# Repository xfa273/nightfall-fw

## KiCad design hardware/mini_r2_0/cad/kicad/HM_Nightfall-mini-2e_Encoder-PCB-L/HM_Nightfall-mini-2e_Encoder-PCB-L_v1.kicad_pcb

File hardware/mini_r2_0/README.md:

# hardware/mini_r2_0

STM32F413 系 mini 新機体 (`mini_r2_0`) のハードウェア情報です。

## 構成

- `cad/`: Eagle 回路図・基板・PDF・DRC ルール
- `cad/eagle/`: Eagle 移行前原本
- `cad/kicad/`: KiCad 移行後の編集原本
- `cad/export/`: PDF、Gerber、実装位置、発注用出力
- `bom/`: 部品表・調達情報
- `notes/`: ピン一覧、ERC/DRC スクリーンショット

## 備考

- 主要ソースは `_sandbox/f413_preorder/` から本ディレクトリへ移行済みです。
- 以後の更新は `hardware/mini_r2_0/` 側を正として管理します。
- 対応する Eagle プロジェクトは `HM_Nightfall-mini-2e` です。
- 対応するソフトウェア側プロファイルは `f413_preorder` です。
- KiCad 10.0.3 で `cad/kicad/HM_Nightfall-mini-2e/` へ初回インポート済みです。
- 初回インポート結果は `notes/kicad/` の ERC/DRC レポートを確認しながらレビューします。
- KiCad レビュー完了までは Eagle 原本と KiCad 原本を併存させ、確認後に `cad/kicad/` を編集正とします。

## KiCad プロジェクト単位

- `cad/kicad/HM_Nightfall-mini-2e/`: 本体基板
- `cad/kicad/HM_Nightfall-mini-2e_Encoder-PCB-L/`: 左エンコーダ基板
- `cad/kicad/HM_Nightfall-mini-2e_Encoder-PCB-R/`: 右エンコーダ基板
- `cad/kicad/STLink-Adapter/`: ST-LINK から機体コネクタへの変換基板
- `cad/kicad/UART-Adapter/`: UART から機体コネクタへの変換基板
- `cad/kicad/WeAct-Adapter-5V/`: WeAct MiniDebugger用、手動5 V遮断スイッチ付き変換基板

各サブ基板は本体基板と独立した小基板のため、KiCad でも 1 基板 1 プロジェクトとして管理します。
- Eagle 9.6.2 で生成した参照アーカイブは `cad/export/reference/eagle_archive_20260606/` に保存しています。

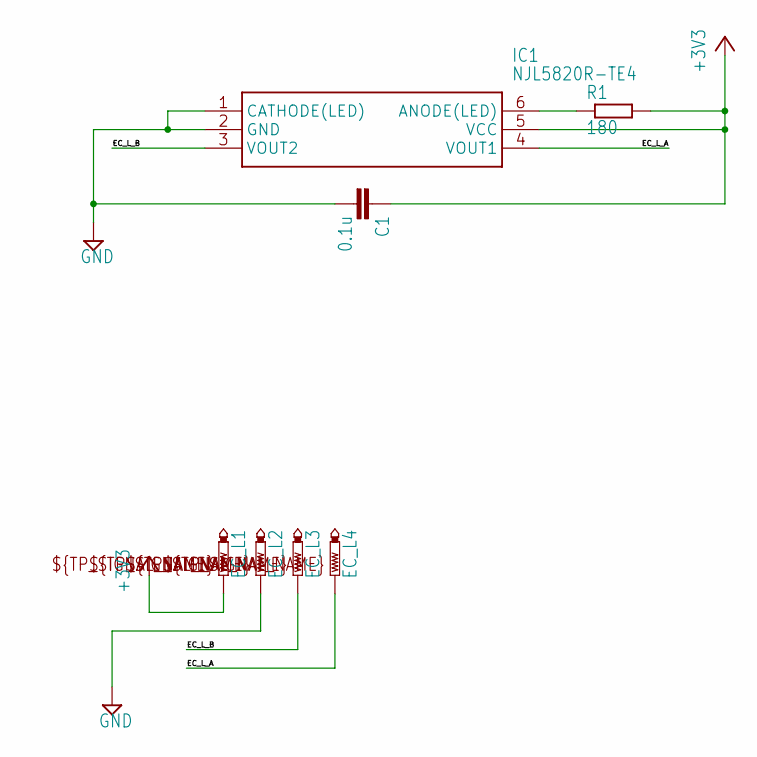
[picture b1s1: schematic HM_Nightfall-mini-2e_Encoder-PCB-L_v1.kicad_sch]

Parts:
C1: 0.1u; C0402
EC_L1, EC_L2, EC_L3, EC_L4: PTR1TP06SQ; TP06SQ
IC1: NJL5820R-TE4; NJL5820RTE4
R1: 180; R0402

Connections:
+3V3: C1.1, EC_L1.TP, IC1.5 (VCC), R1.2
EC_L_A: EC_L4.TP, IC1.4 (VOUT1)
EC_L_B: EC_L3.TP, IC1.3 (VOUT2)
GND: C1.2, EC_L2.TP, IC1.1 (CATHODE(LED)), IC1.2 (GND)
unnamed: IC1.6 (ANODE(LED)), R1.1

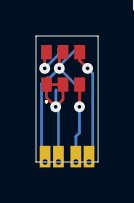
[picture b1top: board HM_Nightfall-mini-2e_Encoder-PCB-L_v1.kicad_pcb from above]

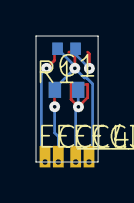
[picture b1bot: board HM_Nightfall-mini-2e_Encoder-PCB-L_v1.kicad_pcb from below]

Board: 2 copper layers, 3.4 x 7.0 mm, 7 parts (6 on the bottom side), 5 nets.

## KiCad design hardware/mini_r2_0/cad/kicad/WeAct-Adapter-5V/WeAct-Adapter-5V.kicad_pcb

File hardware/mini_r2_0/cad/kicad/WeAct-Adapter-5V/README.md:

# WeAct-Adapter-5V

WeAct Studio MiniDebugger から `mini_r2_0` / F413 機体へ SWD、SWO、UART、5 V を接続する変換基板です。
既存の `STLink-Adapter` を基に、デバッガの 5 V 出力を手動で遮断できるスライドスイッチ `SW1` を追加しています。

## 電源スイッチ

- `5V` 側: MiniDebugger の 5 V を機体コネクタ K1 pin 1 へ接続します。
- `OFF` 側: MiniDebugger の 5 V を機体から切り離します。SWD/UART/GND は接続されたままです。
- `SW1` は UART-Adapter と同じ E-Switch `EG1218`（SPDT, On-On）を使用します。中央端子を機体 5 V、`5V` 側端子をデバッガ 5 V、`OFF` 側端子を未接続としています。

> [!CAUTION]
> この基板はダイオードORやロードスイッチによる自動逆流防止回路ではありません。バッテリを接続する前に必ず `OFF` にしてください。`5V` のままバッテリとMiniDebuggerを同時接続しないでください。

`EG1218` の定格は 200 mA / 30 VDC です。このアダプタからの給電はファームウェア書き込み、ログ確認、ブザー等の低消費電力なベンチ作業向けです。モータやファンを動かす用途には使用しません。

## MiniDebugger側の配線

| MiniDebugger信号 | J2 pin | アダプタ | 機体側 |
| --- | --- | --- | --- |
| `5V` | 1 | TP1 pad 1 | K1 pin 1 `+5V`（SW1経由） |
| `TXD` | 4 | TP1 pad 2 | K1 pin 9 `USART1_RX` |
| `RXD` | 3 | TP1 pad 3 | K1 pin 8 `USART1_TX` |
| `GND` | 2 | TP1 pad 4 | K1 pin 2 `GND` |
| `SWDIO` | 9 | TP2 pad 1 | K1 pin 3 `SWDIO` |
| `SWCLK` | 8 | TP2 pad 2 | K1 pin 4 `SWCLK` |
| `SWO` | 6 | TP2 pad 3 | K1 pin 10 `SWO` |

信号名とMiniDebuggerのJ2ピン番号を基準に配線し、コネクタを見たときの物理的な並びだけで判断しないでください。TXD/RXDやSWD信号を5 V/GNDへ誤接続すると、MiniDebuggerのUSB認識が消えるほどの過電流になる場合があります。

MiniDebugger の `3V3`（J2 pin 10）と `NRST`（J2 pin 5）はこのアダプタでは未接続です。余った線は互いに接触しないよう個別に絶縁します。MiniDebugger の2本目の `GND`（J2 pin 7）は未使用でも構いません。

## 初回組立後の確認

最初に機体を接続せず、テスターで次を確認します。

1. `OFF` 側で TP1 pad 1 と K1 pin 1 が導通しないこと。
2. `5V` 側で TP1 pad 1 と K1 pin 1 が導通すること。
3. `5V` 側、`OFF` 側のどちらでも 5 V と GND が短絡していないこと。
4. MiniDebuggerだけを接続し、`5V` 側で K1 pin 1 が約 5 V、`OFF` 側で無給電になること。
5. すべての電源を外して機体側ケーブルを接続し、TP1 pad 4－機体GNDがほぼ0 Ωであること。
6. 同じ状態でTP1 pad 2－機体K1 pin 9、TP2 pad 3－機体K1 pin 10がそれぞれ導通し、5 V/GNDとは短絡していないこと。
7. 最後に機体を接続し、モータ・ファンを動かさずSWD、UART、ブザーを確認すること。

## 検証結果

KiCad 10.0.3 のCLIで確認しています。

- PCB DRC: errors 0、unconnected 0
- DRC warnings: 26（元のSTLink-Adapterと同数。K1の狭ピッチ端子に対する既知のソルダーマスク警告）
- ERC: errors 3、warnings 6（元設計の電源駆動未定義3件とフットプリントライブラリ未登録等。今回追加した配線の未接続・短絡エラーなし）
- 上面・下面3Dレンダリング: `preview/`
- ERC/DRCレポート: `reports/`

### 実機検証（2026-07-27）

初回の外部配線誤りを修正した後、製造した基板とmini_r2_0 / STM32F413機体で次を確認しました。

- `5V` 側で意図どおり5 Vを給電し、`OFF` 側でMiniDebuggerの5 V出力を機体から切り離せること。
- macOSからWeAct MiniDebuggerのST-LINK/V2-1（V2J43M28）を認識できること。
- SWD 4000 kHzでターゲット電圧3.22 V、Device ID `0x463`（STM32F413/F423）を読み取り、software resetが成功すること。
- Virtual COM Portを921600 baud / 8N1で開き、安全なUART診断 `i` に対して `[HW-TEST][IMU] WHO_AM_I=0x6B expected=0x6B => PASS` が返ること。

この確認ではモータ・ファンを動作させず、ファームウェア書き込みおよびNVM書き込みも実施していません。

## 発注データ

`fabrication/WeAct-Adapter-5V-gerbers.zip` を基板メーカーへ投入します。

推奨指定:

- 2 layer
- FR-4, 1.6 mm
- 1 oz copper
- HASL lead-free（または通常HASL）
- Solder mask / silkscreen: 任意色

`fabrication/generate_fab.sh` でGerber、Excellon drill、ZIPを再生成できます。

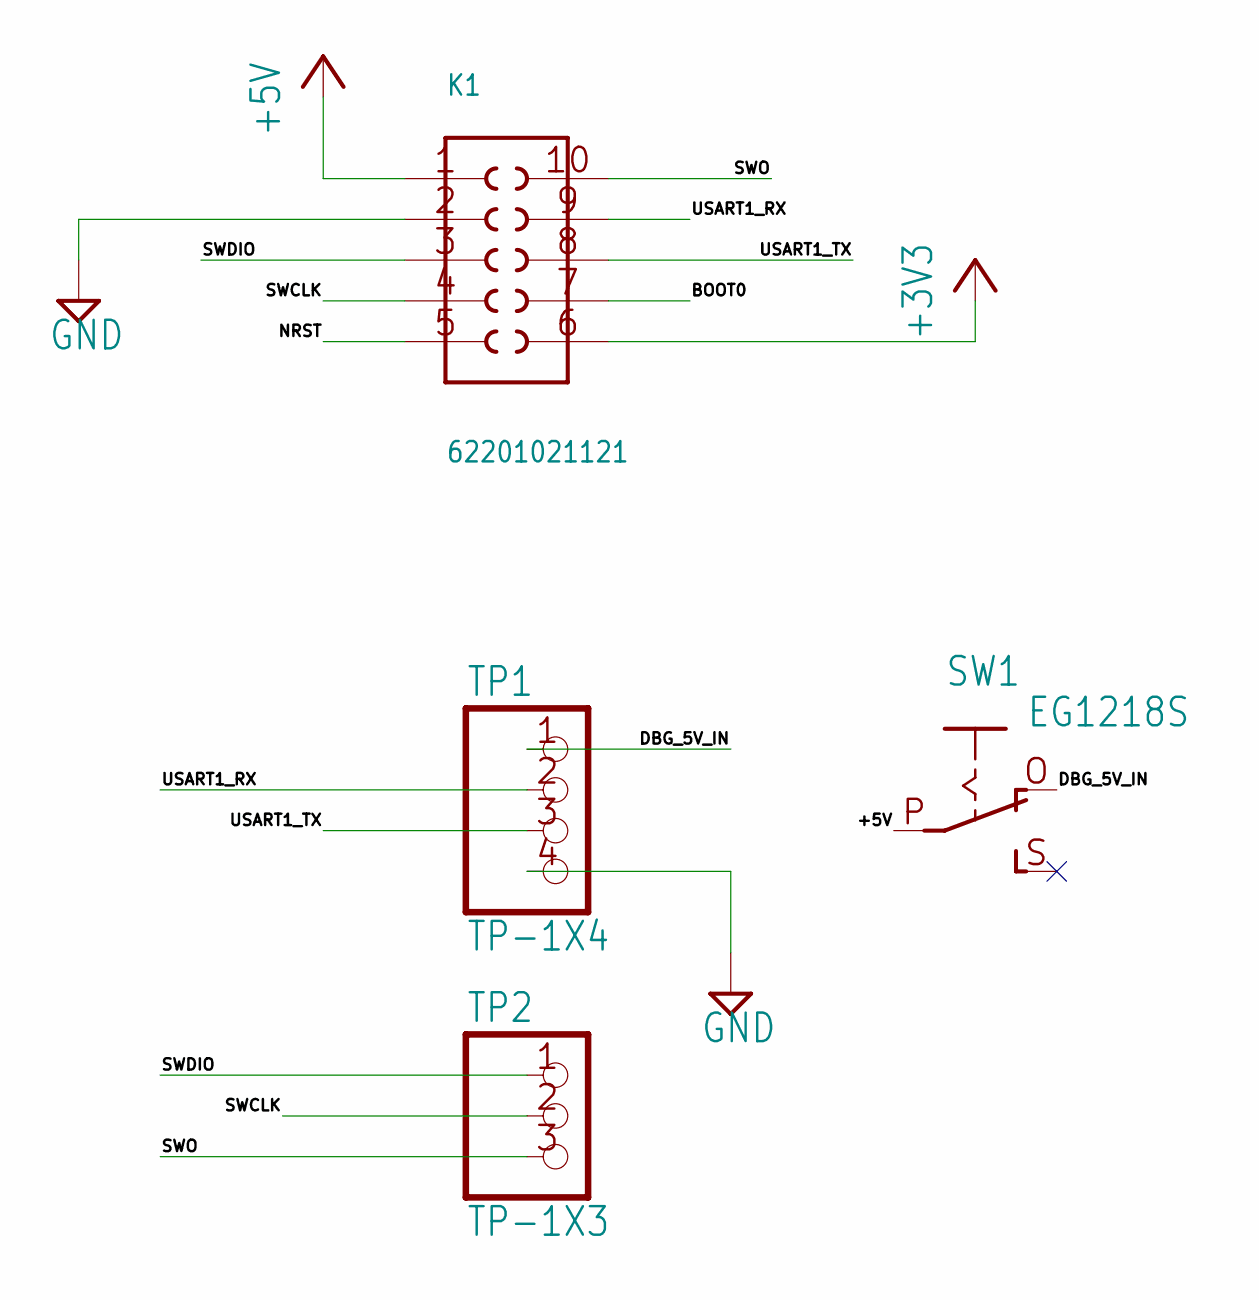
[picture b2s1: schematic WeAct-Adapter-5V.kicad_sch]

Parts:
K1: 62201021121
SW1: EG1218S; EG1218
TP1: TP-1X4; 1X04
TP2: TP-1X3; 1X03

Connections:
+3V3: K1.6
+5V: K1.1, SW1.P
BOOT0: K1.7
DBG_5V_IN: SW1.O, TP1.1
GND: K1.2, TP1.4
NRST: K1.5
SWCLK: K1.4, TP2.2
SWDIO: K1.3, TP2.1
SWO: K1.10, TP2.3
USART1_RX: K1.9, TP1.2
USART1_TX: K1.8, TP1.3

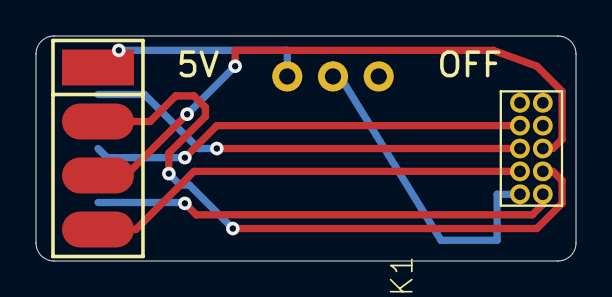
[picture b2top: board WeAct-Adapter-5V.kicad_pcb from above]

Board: 2 copper layers, 30.0 x 12.5 mm, 4 parts (1 on the bottom side), 8 nets.

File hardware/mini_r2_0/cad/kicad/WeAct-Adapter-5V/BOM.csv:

Reference,Quantity,Manufacturer,Manufacturer Part Number,Description,Notes
SW1,1,E-Switch,EG1218,"SPDT On-On through-hole slide switch, 200 mA 30 VDC","Same switch as UART-Adapter"
K1,1,Wurth Elektronik,62201021121,"WR-PHD 1.27 mm dual-row 10-pin header","Confirm mating orientation before soldering"

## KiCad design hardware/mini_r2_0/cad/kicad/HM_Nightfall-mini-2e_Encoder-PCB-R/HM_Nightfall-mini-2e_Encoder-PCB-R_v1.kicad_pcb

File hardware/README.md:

# hardware/

このディレクトリは、機体ごとのハードウェア設計情報の正式置き場です。

## ディレクトリ規約

- `hardware/<board_name>/cad/`: 回路図・基板・設計ルール
- `hardware/<board_name>/cad/eagle/`: Eagle 移行前原本
- `hardware/<board_name>/cad/kicad/`: KiCad 移行後の編集原本
- `hardware/<board_name>/cad/export/`: PDF、Gerber、実装位置、発注用出力
- `hardware/<board_name>/bom/`: 部品表・発注情報
- `hardware/<board_name>/notes/`: 設計メモ・確認結果

`board_name` は `mini_r1_0` のように `<family>_r<major>_<minor>` を使用します。

## Git管理方針

- Eagle の `.sch` / `.brd` / `.dru` / `.cam` と KiCad の `.kicad_pro` / `.kicad_sch` / `.kicad_pcb` は原本として管理します。
- Eagle の `.s#1` / `.b#1` / `.l#1` などの自動バックアップと、KiCad のローカル状態・自動バックアップは管理しません。
- 発注用の Gerber zip や PDF は、再現性が必要な発注版だけを `cad/export/` または GitHub Release で管理します。
- Eagle が使えるうちに確保した旧設計の参照アーカイブは `cad/export/reference/eagle_archive_YYYYMMDD/` に置きます。
- 旧設計や大きな archive は現役基板と分け、必要に応じて別リポジトリ化します。

## 現在の公式配置

- `hardware/mini_r2_0/`: `f413_preorder` / STM32F413 搭載ハーフサイズ / Eagle `HM_Nightfall-mini-2e`
- `hardware/mini_r1_0/`: STM32F405 搭載ハーフサイズ最終版 / Eagle `HM_Nightfall-mini_v1`
- `hardware/classic_r1_0/`: STM32F405 搭載クラシックサイズ最終版 / Eagle `CM_Nightfall-Air_v1`

上記以外の Eagle プロジェクトは旧機体の参考資料として扱い、現役基板とは分けて保管します。

`_sandbox/` 配下は実験・一時作業用とし、正式成果物は本ディレクトリに集約します。

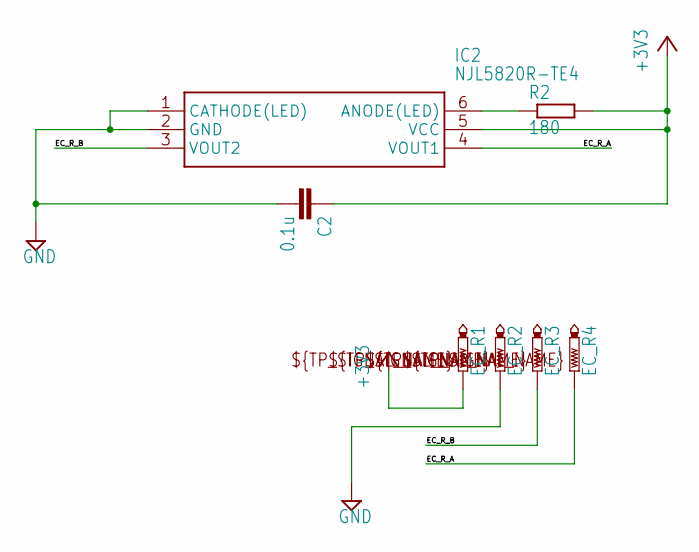
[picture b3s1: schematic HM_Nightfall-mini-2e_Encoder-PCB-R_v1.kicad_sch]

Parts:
C2: 0.1u; C0402
EC_R1, EC_R2, EC_R3, EC_R4: PTR1TP06SQ; TP06SQ
IC2: NJL5820R-TE4; NJL5820RTE4
R2: 180; R0402

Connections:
+3V3: C2.1, EC_R1.TP, IC2.5 (VCC), R2.2
EC_R_A: EC_R4.TP, IC2.4 (VOUT1)
EC_R_B: EC_R3.TP, IC2.3 (VOUT2)
GND: C2.2, EC_R2.TP, IC2.1 (CATHODE(LED)), IC2.2 (GND)
unnamed: IC2.6 (ANODE(LED)), R2.1

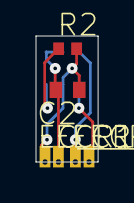
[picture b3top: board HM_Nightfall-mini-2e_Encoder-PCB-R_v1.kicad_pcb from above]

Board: 2 copper layers, 3.4 x 7.0 mm, 7 parts (1 on the bottom side), 5 nets.

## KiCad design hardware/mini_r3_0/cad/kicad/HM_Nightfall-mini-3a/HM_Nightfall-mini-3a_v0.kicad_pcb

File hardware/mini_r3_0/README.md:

# hardware/mini_r3_0

Nightfall mini 3a (`mini_r3_0`) の手動アートワーク開始用データです。

## 開き方

KiCad 10 で次のプロジェクトファイルを開いてください。

`cad/kicad/HM_Nightfall-mini-3a/HM_Nightfall-mini-3a_v0.kicad_pro`

プロジェクトディレクトリには回路図、PCB、設計ルール、ローカルのシンボル／
フットプリントライブラリを同梱しています。別のチェックアウトに依存せず編集できます。

## 引き渡し状態

- 回路図: ERC 0
- PCB: 4層 (`F.Cu / In1.Cu / In2.Cu / B.Cu`)
- 外形、取付穴、機構シルク: 導入済み
- 部品: 102個を配置済み
- 配線、ビア、ゾーン: 0（手動配線開始前）
- U5: 下面露出パッドを使わない手はんだ向けフットプリント
- PCBパッドネット: 最新回路図から再同期済み

未配線なので、PCB DRCの未接続表示が228件あるのは正常です。配線前の物理DRCには
clearance、short、hole、track-crossing、copper-edgeの違反はありません。残る警告は
ライブラリコピー差分とシルク／テキスト由来です。

## 4層の使い方

- `F.Cu / B.Cu`: 部品接続、高電流経路、局所信号
- `In1.Cu`: `GND / GND2` の分割基準面（信号トラックは置かない）
- `In2.Cu`: 低電流信号と `+3V3`
- `GND` と `GND2` は `R0` だけで接続
- 通常信号は 0.20 mm、通常viaは 0.60/0.30 mm
- QFN直近だけ 0.16 mm、局所toe viaは 0.40/0.20 mm
- モータ／ファン約2 A枝は原則0.80 mm以上、集約VBATは1.0 mm以上

回路と電源ドメインの詳細は `notes/POWER_ARCHITECTURE.md` を参照してください。

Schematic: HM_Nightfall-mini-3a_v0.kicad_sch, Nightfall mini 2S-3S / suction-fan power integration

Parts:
C1, C2, C5, C6, C8, C21: 0.1u; C_0402_1005Metric
C3, C15: 2.2u; C0402
C7, C9, C22: 10u/25V X7R; C_0805_2012Metric
C14: 1u; C0402
C23: 22u/10V X7R; C_0805_2012Metric
C24: 0.1u/25V X7R; C_0402_1005Metric
C25: 100nF X7R; C_0402_1005Metric
C_MCU0, C_MCU1, C_MCU2, C_MCU3: 0.1u; C_0402_1005Metric
C_MCU-C0: 2.2u; C_0402_1005Metric
C_MCU-M0: 4.7u; C0402
D3, D4: BAS16WT1GW; SOT323
D5: BZT52-C15S_R1_00001; D_SOD-323
EC_L1, EC_L2, EC_L3, EC_L4: PTR1TP06SQ; TP06SQ
EC_R1, EC_R2, EC_R3, EC_R4: PTR1TP06SQ; TP06SQ
IR_LED_FL0: LED3MM
IR_LED_FR0: LED3MM
IR_LED_L0: LED3MM
IR_LED_R0: LED3MM
J2: FAN_2S3S; FAN_WIRE_PADS_2P
K1: 62201021121
LED1, LED2, LED3: LEDCHIPLED_0603; CHIPLED_0603
MODE0: TL6330AF200Q; SW_TL6330AF200Q
P1: BATTERY; JST_PH2
P-LED0: LEDCHIPLED_0603; CHIPLED_0603
POWER0: EG1215AA; SW_EG1215AA
PT_FL0: LED3MM
PT_FR0: LED3MM
PT_L0: LED3MM
PT_R0: LED3MM
Q2: PJS6403_S1_00001; SOT-23-6
Q3: IRLML6344TRPBF; SOT-23
R0: 0; R0402
R1, R2, R3, R4FL0, R4FR0, R4L0, R4R0, R6, R7, R8: 10k; R0402
R1FL0, R1FR0, R1L0, R1R0: 10; R0402
R2FL0, R2FR0, R2L0, R2R0, R26, R27, R28: 1k; R0402
R4, R12: 100k; R0402
R5: 27k; R0402
R25: 1k; R_0402_1005Metric
R29, R31: 100k; R_0402_1005Metric
R30: 24k; R_0402_1005Metric
R32: 10k; R_0402_1005Metric
R33: 4.7k; R0402
R34, R35: 220k; R_0402_1005Metric
RESET0: TL6330AF200Q; SW_TL6330AF200Q
SPK1: SMT-0540-S-R
TP1, TP2, TP3, TP4: TPB1,27; B1,27
U1: AP2210N-3.3TRG1; SOT95P280X145-3N
U2, U3: MP6551GQB-P; QFN-14_MP6551_MNP
U4: ISM330DHCXTR; PQFN50P250X300X86-14N
U5: STM32F413CHU6TRUFQFPN-48_7X7X0P55MM-M; UFQFPN-48_7X7X0P55MM-M_noEP_hand_solder
U6: CY15B108QI-20LPXC; SON65P328X323X55-8N
U7: MPM3610GQV-P; MPM3610_QFN-20_3x5mm
UBUZ0: PJE260N02; SOT50P160X90-3N
UFL0: PJE260N02; SOT50P160X90-3N
UFR0: PJE260N02; SOT50P160X90-3N
UL0: PJE260N02; SOT50P160X90-3N
UR0: PJE260N02; SOT50P160X90-3N

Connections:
+3V3: C1.2, C2.1, C3.1, C5.2, C15.1, C_MCU0.1, C_MCU1.1, C_MCU2.1, C_MCU3.1, C_MCU-M0.1, EC_L1.TP (TP_TP), EC_R1.TP (TP_TP), K1.6, PT_FL0.A, PT_FR0.A, PT_L0.A, PT_R0.A, R1.1, R1FL0.2, R1FR0.2, R1L0.2, R1R0.2, R3.2, R6.1, R7.1, R25.2, U1.2 (VOUT), U4.5 (VDD_IO), U4.8 (VDD), U5.1 (VBAT), U5.9 (VDDA/VREF+), U5.24 (VDD_2), U5.36 (VDD_3), U5.48 (VDD), U6.8 (VDD)
+5V: C14.1, C23.1, D3.3 (K), K1.1, R29.2, SPK1.+ (-), U1.3 (VIN), U7.7 (OUT), U7.8 (OUT), U7.9 (OUT)
/BOOT0: K1.7, R2.1, U5.44 (BOOT0)
/BUZZER_PWM: R8.1, U5.46 (PB9), UBUZ0.1 (G)
/EC_L_A: EC_L4.TP (TP_TP), U5.16 (PA6)
/EC_L_B: EC_L3.TP (TP_TP), U5.17 (PA7)
/EC_R_A: EC_R4.TP (TP_TP), U5.42 (PB6)
/EC_R_B: EC_R3.TP (TP_TP), U5.43 (PB7)
/FAN_NEG_INTERNAL: C24.2, D4.1 (A), J2.1, Q3.3 (D)
/FAN_PWM: Q3.1 (G), R32.1, U5.45 (PB8)
/FRAM_CS: R7.2, U5.29 (PA8), U6.1 (~CS)
/IMU_CS: R6.2, U4.12 (CS), U5.25 (PB12)
/IR_FL: R4FL0.2, U5.4 (PC15-OSC32_OUT), UFL0.1 (G)
/IR_FR: R4FR0.2, U5.2 (PC13), UFR0.1 (G)
/IR_L: R4L0.2, U5.3 (PC14-OSC32_IN), UL0.1 (G)
/IR_R: R4R0.2, U5.41 (PB5), UR0.1 (G)
/LED_1: R26.2, U5.38 (PA15)
/LED_2: R27.2, U5.32 (PA11)
/LED_3: R28.2, U5.6 (PH1)
/MOTOR_L_DIR: U2.5 (IN2), U5.14 (PA4)
/MOTOR_L_OUT1: TP3.TP (TP_TP), U2.1 (OUT1_2), U2.10 (OUT1)
/MOTOR_L_OUT2: TP4.TP (TP_TP), U2.3 (OUT2_2), U2.8 (OUT2)
/MOTOR_L_PWM: U2.13 (IN1), U5.15 (PA5)
/MOTOR_L_SR: R35.2, U2.6 (SR)
/MOTOR_R_DIR: U3.5 (IN2), U5.19 (PB1)
/MOTOR_R_OUT1: TP1.TP (TP_TP), U3.1 (OUT1_2), U3.10 (OUT1)
/MOTOR_R_OUT2: TP2.TP (TP_TP), U3.3 (OUT2_2), U3.8 (OUT2)
/MOTOR_R_PWM: U3.13 (IN1), U5.21 (PB10)
/MOTOR_R_SR: R34.2, U3.6 (SR)
/MOTOR_STBY: U2.4 (EN2), U2.14 (EN1), U3.4 (EN2), U3.14 (EN1), U5.20 (PB2)
/MPM_EN_INTERNAL: R31.1, U7.17 (EN)
/MPM_FB_INTERNAL: R29.1, R30.1, U7.1 (FB)
/MPM_SW_INTERNAL: U7.4 (SW), U7.5 (SW), U7.6 (SW)
/NRST: C21.1, K1.5, RESET0.1, RESET0.2, U5.7 (NRST)
/Net-(D3-A): D3.1 (A), SPK1.- (+), UBUZ0.3 (D)
/Net-(IR_LED_FL0-C): IR_LED_FL0.K (C), UFL0.3 (D)
/Net-(IR_LED_FL0-PadA): IR_LED_FL0.A, R1FL0.1
/Net-(IR_LED_FR0-C): IR_LED_FR0.K (C), UFR0.3 (D)
/Net-(IR_LED_FR0-PadA): IR_LED_FR0.A, R1FR0.1
/Net-(IR_LED_L0-C): IR_LED_L0.K (C), UL0.3 (D)
/Net-(IR_LED_L0-PadA): IR_LED_L0.A, R1L0.1
/Net-(IR_LED_R0-C): IR_LED_R0.K (C), UR0.3 (D)
/Net-(IR_LED_R0-PadA): IR_LED_R0.A, R1R0.1
/Net-(LED1-PadA): LED1.A, R26.1
/Net-(LED2-PadA): LED2.A, R27.1
/Net-(LED3-PadA): LED3.A, R28.1
/Net-(P-LED0-PadA): P-LED0.A, R25.1
/Net-(U5B-VCAP_1): C_MCU-C0.1, U5.22 (VCAP_1)
/Net-(U6-~WP): R1.2, U6.3 (~WP)
/PUSH_IN_1: MODE0.1, MODE0.2, R3.1, U5.5 (PH0-OSC_IN)
/PWR_GATE_INTERNAL: D5.1 (A), Q2.3 (G), R12.1, R33.1
/PWR_SWITCH_RETURN: POWER0.2 (COM), R33.2
/SENSOR_FL: PT_FL0.K (C), R2FL0.2, U5.12 (PA2)
/SENSOR_FR: PT_FR0.K (C), R2FR0.2, U5.10 (PA0)
/SENSOR_L: PT_L0.K (C), R2L0.2, U5.13 (PA3)
/SENSOR_R: PT_R0.K (C), R2R0.2, U5.11 (PA1)
/SPI2_MISO: U4.1 (SDO/SA0), U5.27 (PB14), U6.2 (SO)
/SPI2_MOSI: U4.14 (SDA), U5.28 (PB15), U6.5 (SI)
/SPI2_SCK: U4.13 (SCL), U5.26 (PB13), U6.6 (SCK)
/SWCLK: K1.4, U5.37 (PA14)
/SWDIO: K1.3, U5.34 (PA13)
/SWO: K1.10, U5.39 (PB3)
/USART1_RX: K1.9, U5.31 (PA10)
/USART1_TX: K1.8, U5.30 (PA9)
/VOL_CHECK: C25.1, R4.1, R5.2, U5.18 (PB0)
GND: C1.1, C2.2, C3.2, C5.1, C14.2, C15.2, C21.2, C25.2, C_MCU0.2, C_MCU1.2, C_MCU2.2, C_MCU3.2, C_MCU-C0.2, C_MCU-M0.2, EC_L2.TP (TP_TP), EC_R2.TP (TP_TP), K1.2, LED1.C, LED2.C, P-LED0.C, R0.2, R2.2, R2FL0.1, R2FR0.1, R2L0.1, R2R0.1, R4FL0.1, R4FR0.1, R4L0.1, R4R0.1, R5.1, R8.2, RESET0.3, RESET0.4, U1.1 (GND), U4.2 (SDX), U4.3 (SCX), U4.6 (GND), U4.7 (GND), U5.8 (VSSA/VREF-), U5.23 (VSS_2), U5.35 (VSS_3), U5.47 (VSS), U5.49 (EPAD), U6.4 (VSS), UBUZ0.2 (E), UFL0.2 (E), UFR0.2 (E), UL0.2 (E), UR0.2 (E)
GND2: C6.1, C7.1, C8.1, C9.1, C22.2, C23.2, LED3.C, MODE0.3, MODE0.4, P1.1, POWER0.1 (OFF), Q3.2 (S), R0.1, R30.2, R32.2, R34.1, R35.1, U2.9 (GND), U3.9 (GND), U7.3 (AGND), U7.12 (PGND), U7.13 (PGND), U7.14 (PGND)
VBAT_RAW: D5.2 (K), P1.2, Q2.4 (S), R12.2
VBAT_SW: C6.2, C7.2, C8.2, C9.2, C22.1, C24.1, D4.3 (K), J2.2, Q2.1 (D), Q2.2 (D), Q2.5 (D), Q2.6 (D), R4.2, R31.2, U2.2 (VIN), U3.2 (VIN), U7.16 (IN)

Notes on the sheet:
2S-3S POWER: VBAT_SW -> MPM3610 -> +5V
SUCTION FAN / 2S-3S
2S-3S BATTERY / MAIN SWITCH
Wall Sensor
MCU
Power Supply
SPI Device
Interface
Motor Driver

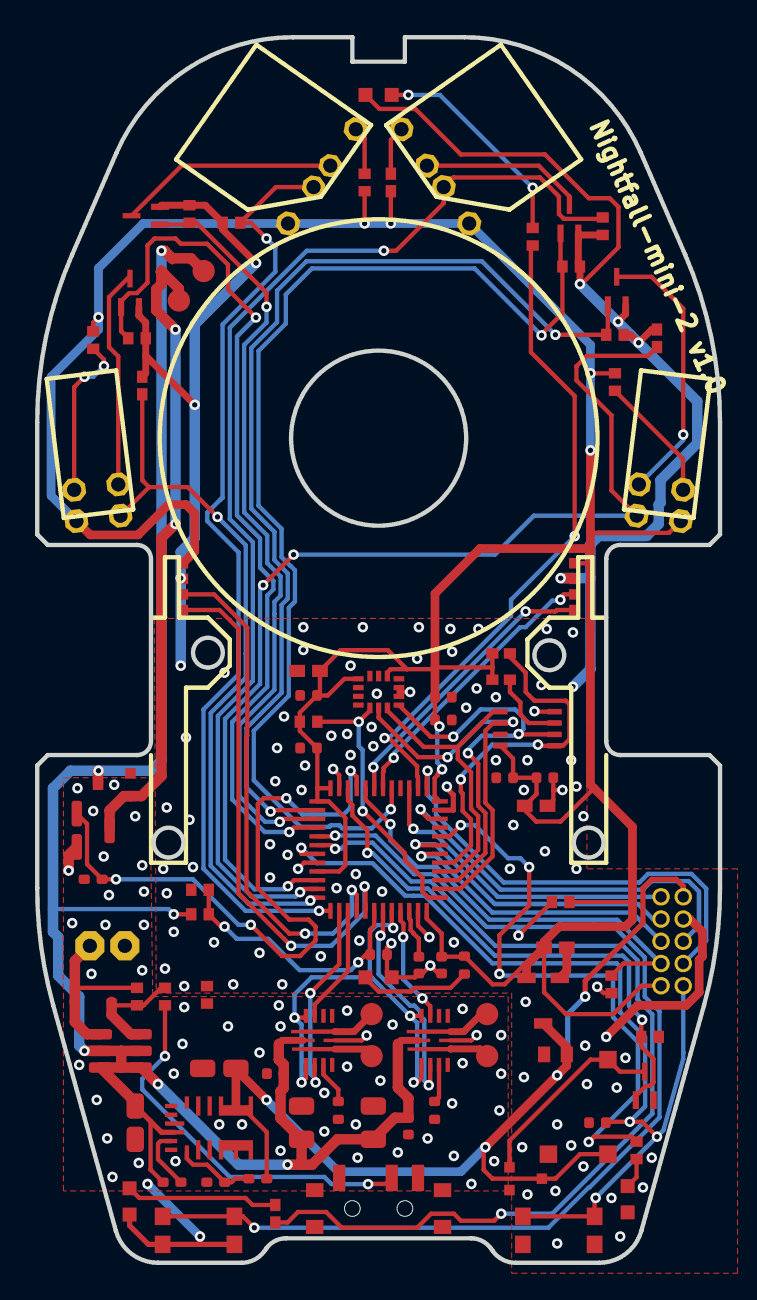
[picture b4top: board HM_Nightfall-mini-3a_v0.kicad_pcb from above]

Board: 2 copper layers, 39.0 x 70.0 mm, 102 parts (0 on the bottom side), 69 nets.

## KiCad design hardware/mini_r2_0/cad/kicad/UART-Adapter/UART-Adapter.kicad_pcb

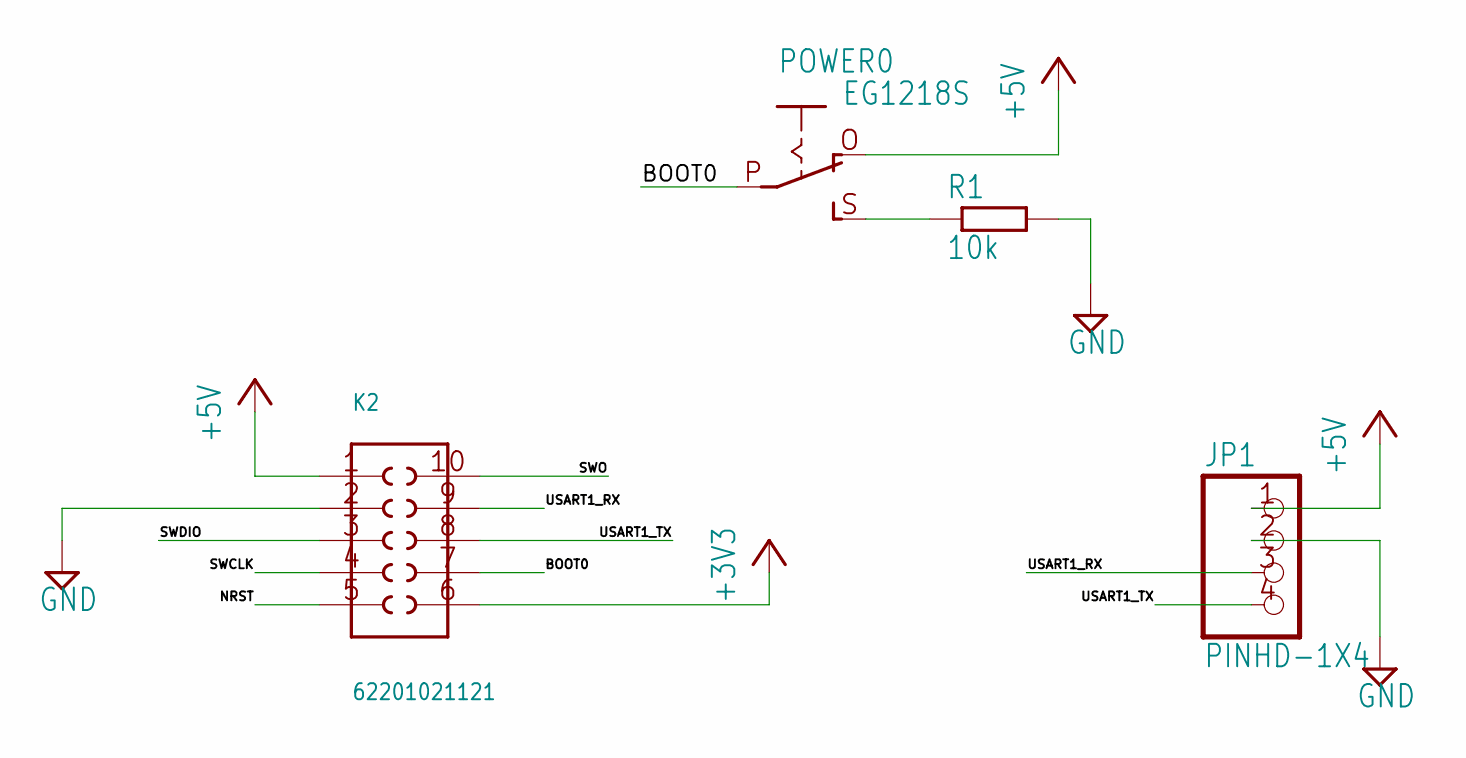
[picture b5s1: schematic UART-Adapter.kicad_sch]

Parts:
JP1: PINHD-1X4; 1X04
K2: 62201021121
POWER0: EG1218S; EG1218
R1: 10k; R0603

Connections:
+3V3: K2.6
+5V: JP1.1, K2.1, POWER0.O
BOOT0: K2.7, POWER0.P
GND: JP1.2, K2.2, R1.2
unnamed: POWER0.S, R1.1
NRST: K2.5
SWCLK: K2.4
SWDIO: K2.3
SWO: K2.10
USART1_RX: JP1.3, K2.9
USART1_TX: JP1.4, K2.8

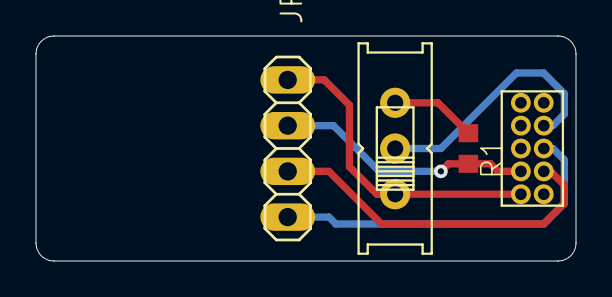
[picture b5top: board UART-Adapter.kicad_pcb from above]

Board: 2 copper layers, 30.0 x 12.5 mm, 4 parts (0 on the bottom side), 6 nets.

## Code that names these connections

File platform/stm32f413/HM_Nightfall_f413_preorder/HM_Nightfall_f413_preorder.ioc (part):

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Mcu.Name=STM32F413C(G-H)Ux
Mcu.Package=UFQFPN48
Mcu.UserName=STM32F413CHUx
PA0.GPIOParameters=GPIO_Label
PA0.GPIO_Label=SENSOR_FR
PA0.Signal=ADCx_IN0
PA1.GPIOParameters=GPIO_Label
PA1.GPIO_Label=SENSOR_R
PA1.Signal=ADCx_IN1
PA10.Mode=Asynchronous
PA10.Signal=USART1_RX
PA11.GPIOParameters=GPIO_Label
PA11.GPIO_Label=LED_2
PA11.Signal=GPIO_Output
PA13.Mode=Trace_Asynchronous_SW
PA13.Signal=SYS_JTMS-SWDIO
PA14.Mode=Trace_Asynchronous_SW
PA14.Signal=SYS_JTCK-SWCLK
PA15.GPIOParameters=GPIO_Label
PA15.GPIO_Label=LED_1
PA15.Signal=GPIO_Output
PA2.GPIOParameters=GPIO_Label
PA2.GPIO_Label=SENSOR_FL
PA2.Signal=ADCx_IN2
PA3.GPIOParameters=GPIO_Label
PA3.GPIO_Label=SENSOR_L
PA3.Signal=ADCx_IN3
PA4.GPIOParameters=GPIO_Label
PA4.GPIO_Label=MOTOR_L_DIR
PA4.Signal=GPIO_Output
PA5.GPIOParameters=GPIO_Label
PA5.GPIO_Label=MOTOR_L_PWM
PA5.Signal=S_TIM2_CH1_ETR
PA6.GPIOParameters=GPIO_Label
PA6.GPIO_Label=EC_L_A
PA6.Signal=S_TIM3_CH1
PA7.GPIOParameters=GPIO_Label
PA7.GPIO_Label=EC_L_B
PA7.Signal=S_TIM3_CH2
PA8.GPIOParameters=GPIO_Label
PA8.GPIO_Label=FRAM_CS
PA8.Signal=GPIO_Output
PA9.Mode=Asynchronous
PA9.Signal=USART1_TX
PB0.GPIOParameters=GPIO_Label
PB0.GPIO_Label=VOL_CHECK
PB0.Signal=ADCx_IN8
PB1.GPIOParameters=GPIO_Label
PB1.GPIO_Label=MOTOR_R_DIR
PB1.Signal=GPIO_Output
PB10.GPIOParameters=GPIO_Label
PB10.GPIO_Label=MOTOR_R_PWM
PB10.Signal=S_TIM2_CH3
PB12.GPIOParameters=GPIO_Label
PB12.GPIO_Label=IMU_CS
PB12.Signal=GPIO_Output
PB13.Mode=Full_Duplex_Master
PB13.Signal=SPI2_SCK
PB14.Mode=Full_Duplex_Master
PB14.Signal=SPI2_MISO
PB15.Mode=Full_Duplex_Master
PB15.Signal=SPI2_MOSI
PB2.GPIOParameters=GPIO_Label
PB2.GPIO_Label=MOTOR_STBY
PB2.Signal=GPIO_Output
PB3.Mode=Trace_Asynchronous_SW
PB3.Signal=SYS_JTDO-SWO
PB5.GPIOParameters=GPIO_Label
PB5.GPIO_Label=IR_R
PB5.Signal=GPIO_Output
PB6.GPIOParameters=GPIO_Label
PB6.GPIO_Label=EC_R_A
PB6.Signal=S_TIM4_CH1
PB7.GPIOParameters=GPIO_Label
PB7.GPIO_Label=EC_R_B
PB7.Signal=S_TIM4_CH2
PB8.GPIOParameters=GPIO_Label
PB8.GPIO_Label=FAN_PWM
PB8.Signal=S_TIM10_CH1
PB9.GPIOParameters=GPIO_Label
PB9.GPIO_Label=BUZZER_PWM
PB9.Signal=S_TIM11_CH1
PC13.GPIOParameters=GPIO_Label
PC13.GPIO_Label=IR_FR
PC13.Signal=GPIO_Output
PC14-OSC32_IN.GPIOParameters=GPIO_Label
PC14-OSC32_IN.GPIO_Label=IR_L
PC14-OSC32_IN.Signal=GPIO_Output
PC15-OSC32_OUT.GPIOParameters=GPIO_Label
PC15-OSC32_OUT.GPIO_Label=IR_FL
PC15-OSC32_OUT.Signal=GPIO_Output
PH0\ -\ OSC_IN.GPIOParameters=GPIO_Label
PH0\ -\ OSC_IN.GPIO_Label=PUSH_IN_1
PH0\ -\ OSC_IN.Signal=GPIO_Input
PH1\ -\ OSC_OUT.GPIOParameters=GPIO_Label
PH1\ -\ OSC_OUT.GPIO_Label=LED_3
PH1\ -\ OSC_OUT.Signal=GPIO_Output
RCC.SYSCLKFreq_VALUE=100000000
RCC.SYSCLKSource=RCC_SYSCLKSOURCE_PLLCLK
board=custom
